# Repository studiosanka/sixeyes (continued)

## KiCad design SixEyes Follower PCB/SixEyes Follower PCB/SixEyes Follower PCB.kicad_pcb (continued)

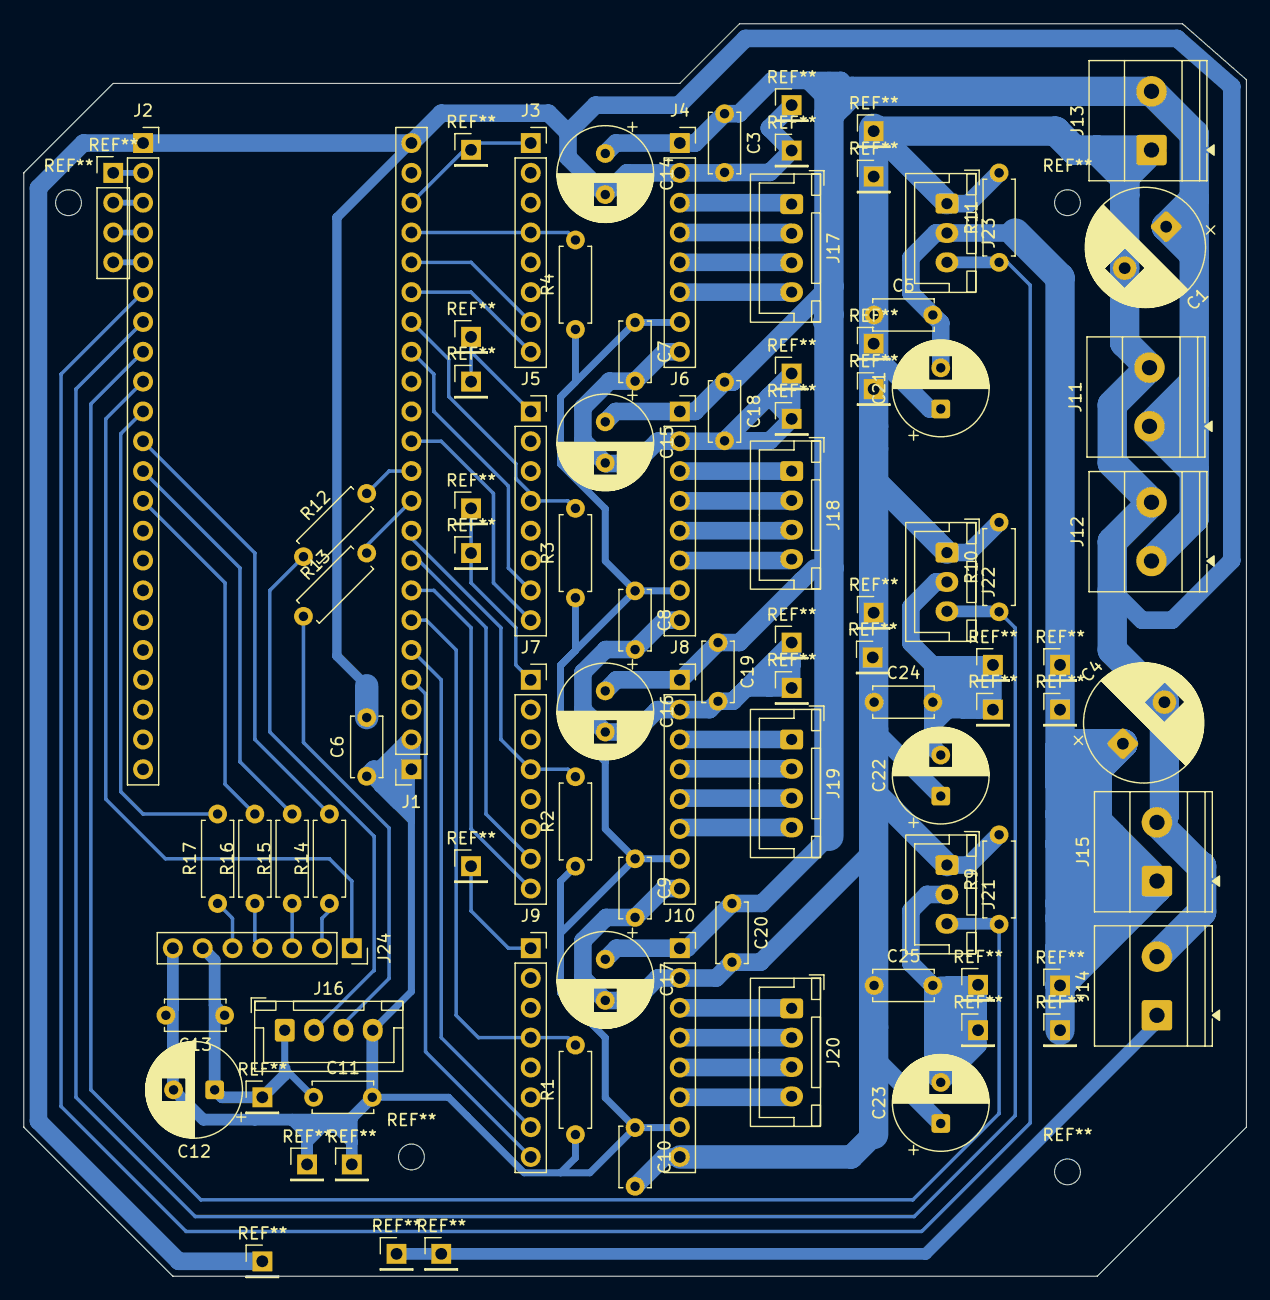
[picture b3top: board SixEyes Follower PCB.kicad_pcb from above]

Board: 2 copper layers, 104.1 x 106.7 mm, 61 parts (0 on the bottom side), 43 nets.

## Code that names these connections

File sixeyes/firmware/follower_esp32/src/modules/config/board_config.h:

// Board and system configuration constants
#pragma once

// Safety defaults
static constexpr unsigned long SAFETY_HEARTBEAT_TIMEOUT_MS =
    500; // default ~500 ms

// Control loop frequency (Hz) - choose between 200 and 500
static constexpr int CONTROL_LOOP_HZ = 400;

// Motor/driver counts
static constexpr int NUM_STEPPERS = 4;
static constexpr int NUM_SERVOS = 3;

// Leader-Follower dedicated UART pins (Follower side)
// Per "SixEyes Technical Reference 2":
//   RX (Leader TX) -> GPIO18
//   TX (Leader RX) -> GPIO17
static constexpr int LEADER_UART_RX_PIN = 18;
static constexpr int LEADER_UART_TX_PIN = 17;

// SD SPI + card-detect pins (Follower side)
static constexpr int SD_MOSI_PIN = 35;
static constexpr int SD_SCK_PIN = 36;
static constexpr int SD_MISO_PIN = 37;
static constexpr int SD_CS_PIN = 38;
static constexpr int SD_CD_PIN = 39;

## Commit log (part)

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2026-05-11 docs(hardware): add follower NodeMesh PCB design package
2026-05-11 docs(hardware): add SD reader SPI pinout and through-hole wiring details
2026-05-11 docs(hardware): add explicit devboard header footprints for ESP32-S3 and TMC2209
2026-05-11 docs(hardware): add schematic symbol definitions for follower PCB package
2026-05-12 docs(hardware): add leader ESP32-C6 SuperMini PCB design package
2026-05-14 leader: remap ADC pots to GPIO0-4,6 and update docs
2026-05-14 chore: split NodeMesh into dedicated repo and add redirects
2026-05-14 docs(hardware): update follower nodemesh PCB design package
2026-05-21 hardware: remap TMC2209 to 6-wire JST pinout
2026-05-21 Update follower pinout mapping in firmware and hardware docs
2026-05-28 docs: clarify repo boundaries and consolidate overlapping guides
2026-05-28 chore: remove deprecated nodemesh and camera folders from sixeyes
2026-05-30 refactor: flatten sixeyes/ to root, add KiCad PCB project, fix JSON pipeline, fix safety bitmask, implement ROS2 nodes, update docs
    - Flatten sixeyes/ wrapper: firmware/, ros2_ws/, tools/, simulation/, hardware_assets/ now at repo root
    - Merge sixeyes/docs/ into docs/ (safety.md, protocols/uart_protocol.md)
    - Add KiCad follower PCB project files (.kicad_pro, .kicad_prl, fp-lib-table, custom footprints, design_inputs/)
    - Update .gitignore: exclude KiCad .history/ and *-backups/ directories
    - Fix UartJsonParser pipeline: init() now called in MessageRouter::init(), update() ticked each control loop iteration
    - Add JOINT_STATE (type 8) to MessageType enum, parse block, struct, and TeleoperationH
2026-05-30 chore: remove stale files, build artifacts, and completed planning docs
    - Remove firmware/follower_esp32/build.log (binary build artifact)
    - Remove firmware/follower_esp32/src/modules/comm/protocol.md (stub pointing to canonical doc)
    - Remove docs/DOC_CONSOLIDATION_PLAN.md (consolidation is complete)
    - Remove docs/safety.md (7-line stub with stale path; content in README + HARDWARE_VALIDATION.md)
    - Remove docs/archive/sixeyes/ (archived old full versions; canonical condensed versions in docs/firmware/ and docs/references/)
    - Update .gitignore: add build.log and .pio/ patterns
2026-05-30 fix: resolve P0/P1/P2 deployment blockers
    P0 - ROS2 launch files:
    - Add sixeyes_bringup package with teleop.launch.py (4 nodes) and vla.launch.py (5 nodes)
    - Operators can now start the entire system with one command
    P0 - VLACommandHandler::handleCommand():
    - Now validates against known VLA command names; returns false for unknown commands
    - Explicit MODE_CHANGE rejection with helpful recompile message
2026-06-08 Alpha/Beta development, June 2026
    Combines the work from 4 to 8 June 2026: restructuring the firmware into Alpha and Beta
    variants, the Beta follower and leader PCB design packages and KiCad parts, the technical
    reference and documentation rewrite, the CERN-OHL-S hardware licence, open-loop stepper
    mitigation strategies for the Beta firmware, and the project credits.
